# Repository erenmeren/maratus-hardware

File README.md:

# maratus-hardware

Open hardware for **Maratus** (maratus.co): the **Core** (an always-powered 4-inch touchscreen that
shows a cloud-triggered QR code), the **Dock** and the **LAN Module**. KiCad sources, mechanical
CAD and design documents.

**Status: draft.** Nothing here is manufacturing-ready, and no hardware has been built or tested.
The boards are generated and autorouted; the critical nets still need a layout engineer
(`docs/design-spec.md`, sections 10 and 11).

## Where to start

| Path | Content |
| --- | --- |
| `docs/design-spec.md` | The design decisions, block by block, and the open items |
| `hardware/core/` | KiCad project of the Core |
| `hardware/dock-contact/`, `hardware/dock-base/` | KiCad projects of the Dock's two boards |
| `mechanical/core/` | Enclosure (STEP, STL), cover lens (DXF and drawing) |
| `tools/` | Generators and checks; the commands are listed in `CLAUDE.md` |

Related repositories: `erenmeren/maratus-firmware` (ESP-IDF firmware) and `erenmeren/maratus-admin`
(cloud, device protocol).

## Licence

Apache License 2.0, see `LICENSE`. Copyright 2026 the Maratus authors.

Not covered by it: the datasheets and reference schematics in `docs/reference/`, which belong to
their manufacturers and are kept here for reference, and Espressif's KiCad library in
`hardware/lib/espressif`, a git submodule with its own licence.

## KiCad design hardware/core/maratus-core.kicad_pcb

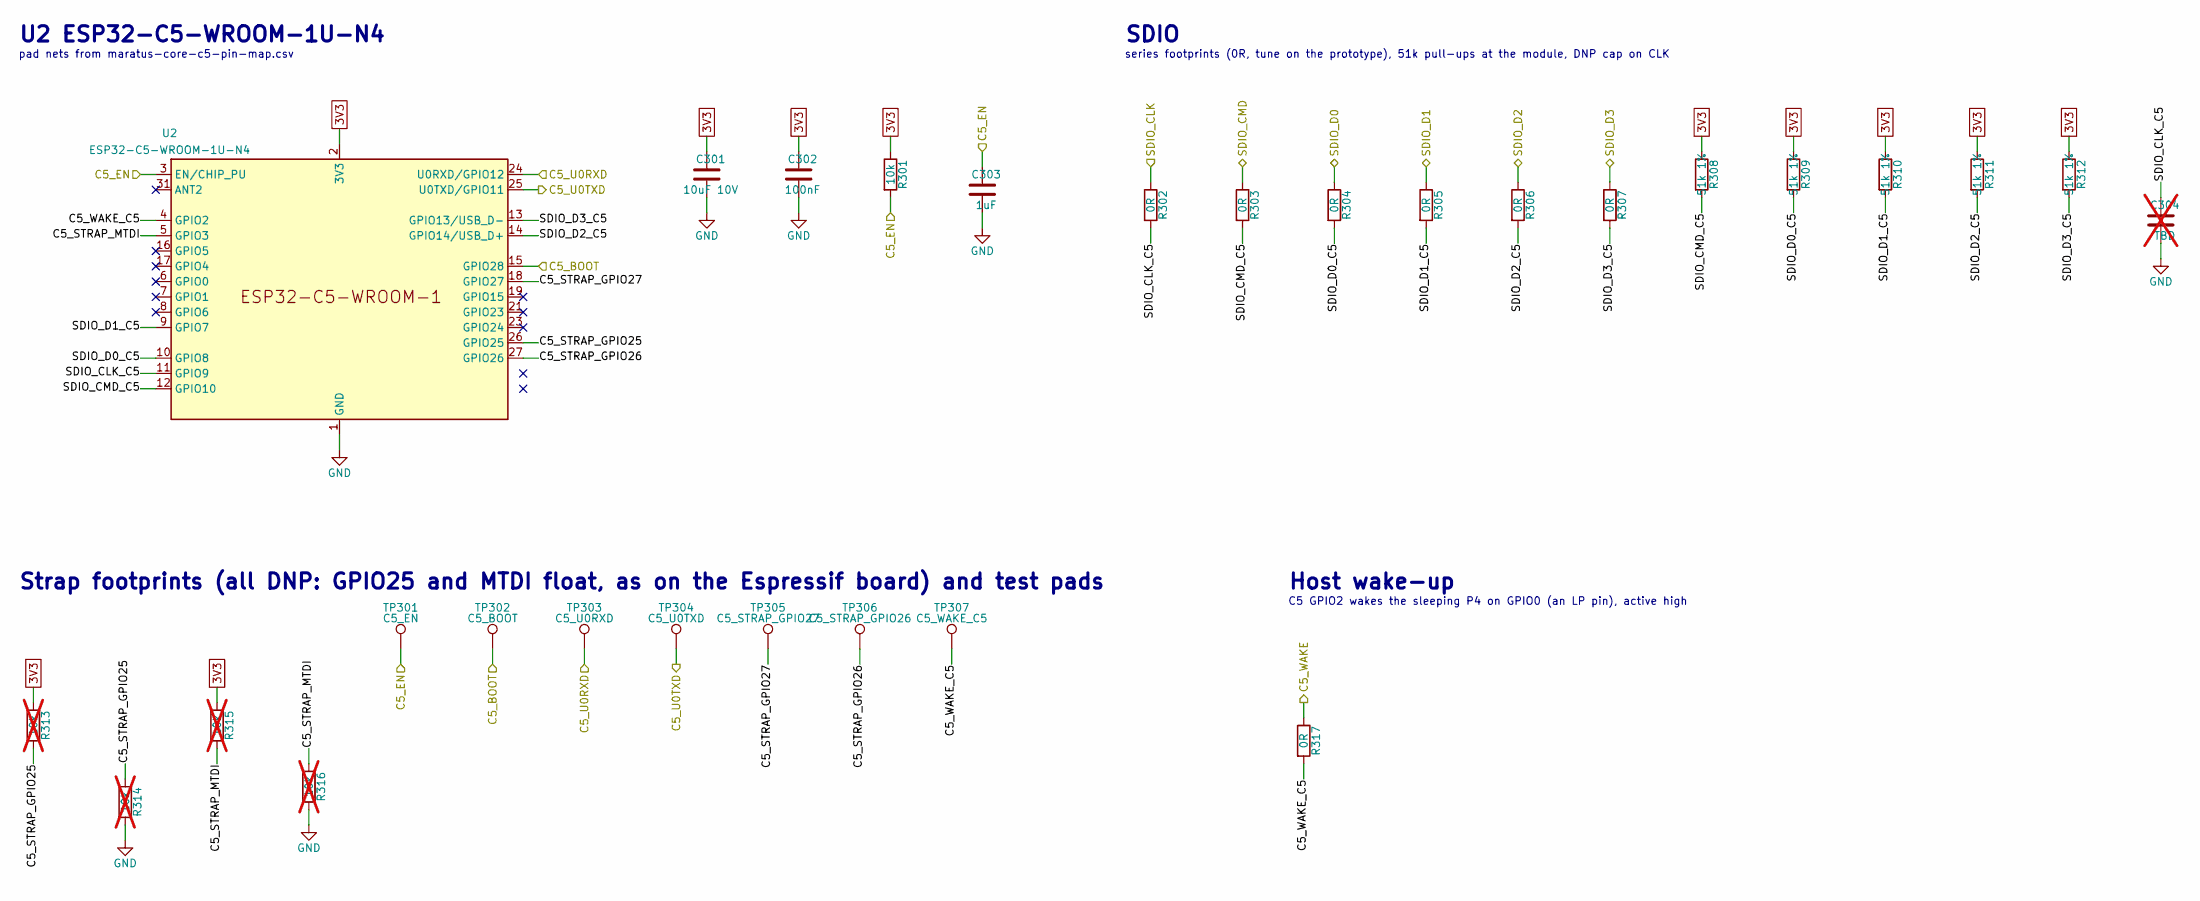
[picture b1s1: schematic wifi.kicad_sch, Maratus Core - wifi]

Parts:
C301: 10uF 10V; C_0805_2012Metric
C302: 100nF; C_0402_1005Metric
C303: 1uF; C_0402_1005Metric
C304: TBD; C_0402_1005Metric; not fitted
R301: 10k; R_0402_1005Metric
R302, R303, R304, R305, R306, R307, R317: 0R; R_0402_1005Metric
R308, R309, R310, R311, R312: 51k 1%; R_0402_1005Metric
R313, R314, R315, R316: 10k; R_0402_1005Metric; not fitted
TP301: C5_EN; TestPoint_Pad_D1.0mm
TP302: C5_BOOT; TestPoint_Pad_D1.0mm
TP303: C5_U0RXD; TestPoint_Pad_D1.0mm
TP304: C5_U0TXD; TestPoint_Pad_D1.0mm
TP305: C5_STRAP_GPIO27; TestPoint_Pad_D1.0mm
TP306: C5_STRAP_GPIO26; TestPoint_Pad_D1.0mm
TP307: C5_WAKE_C5; TestPoint_Pad_D1.0mm
U2: ESP32-C5-WROOM-1U-N4; ESP32-C5-WROOM-1U

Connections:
3V3: C301.1, C302.1, R301.1, R308.1, R309.1, R310.1, R311.1, R312.1, R313.1, R315.1, U2.2 (3V3); also elsewhere on the board
/C5_BOOT: TP302.1, U2.15 (GPIO28); also elsewhere on the board
/C5_EN: C303.1, R301.2, TP301.1, U2.3 (EN/CHIP_PU); also elsewhere on the board
/C5_U0RXD: TP303.1, U2.24 (U0RXD/GPIO12); also elsewhere on the board
/C5_U0TXD: TP304.1, U2.25 (U0TXD/GPIO11); also elsewhere on the board
/C5_WAKE: R317.1; also elsewhere on the board
/SDIO_CLK: R302.1; also elsewhere on the board
/SDIO_CMD: R303.1; also elsewhere on the board
/SDIO_D0: R304.1; also elsewhere on the board
/SDIO_D1: R305.1; also elsewhere on the board
/SDIO_D2: R306.1; also elsewhere on the board
/SDIO_D3: R307.1; also elsewhere on the board
/wifi/C5_STRAP_GPIO25: R313.2, R314.1, U2.26 (GPIO25)
/wifi/C5_STRAP_GPIO26: TP306.1, U2.27 (GPIO26)
/wifi/C5_STRAP_GPIO27: TP305.1, U2.18 (GPIO27)
/wifi/C5_STRAP_MTDI: R315.2, R316.1, U2.5 (GPIO3)
/wifi/C5_WAKE_C5: R317.2, TP307.1, U2.4 (GPIO2)
/wifi/SDIO_CLK_C5: C304.1, R302.2, U2.11 (GPIO9)
/wifi/SDIO_CMD_C5: R303.2, R308.2, U2.12 (GPIO10)
/wifi/SDIO_D0_C5: R304.2, R309.2, U2.10 (GPIO8)
/wifi/SDIO_D1_C5: R305.2, R310.2, U2.9 (GPIO7)
/wifi/SDIO_D2_C5: R306.2, R311.2, U2.14 (GPIO14/USB_D+)
/wifi/SDIO_D3_C5: R307.2, R312.2, U2.13 (GPIO13/USB_D-)
GND: C301.2, C302.2, C303.2, C304.2, R314.2, R316.2, U2.1 (GND), U2.28 (GND), U2.29 (GND), U2.30 (GND), U2.32 (GND); also elsewhere on the board

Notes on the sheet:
SDIO
U2 ESP32-C5-WROOM-1U-N4
C5 GPIO2 wakes the sleeping P4 on GPIO0 (an LP pin), active high
Host wake-up
Strap footprints (all DNP: GPIO25 and MTDI float, as on the Espressif board) and test pads
pad nets from maratus-core-c5-pin-map.csv
series footprints (0R, tune on the prototype), 51k pull-ups at the module, DNP cap on CLK

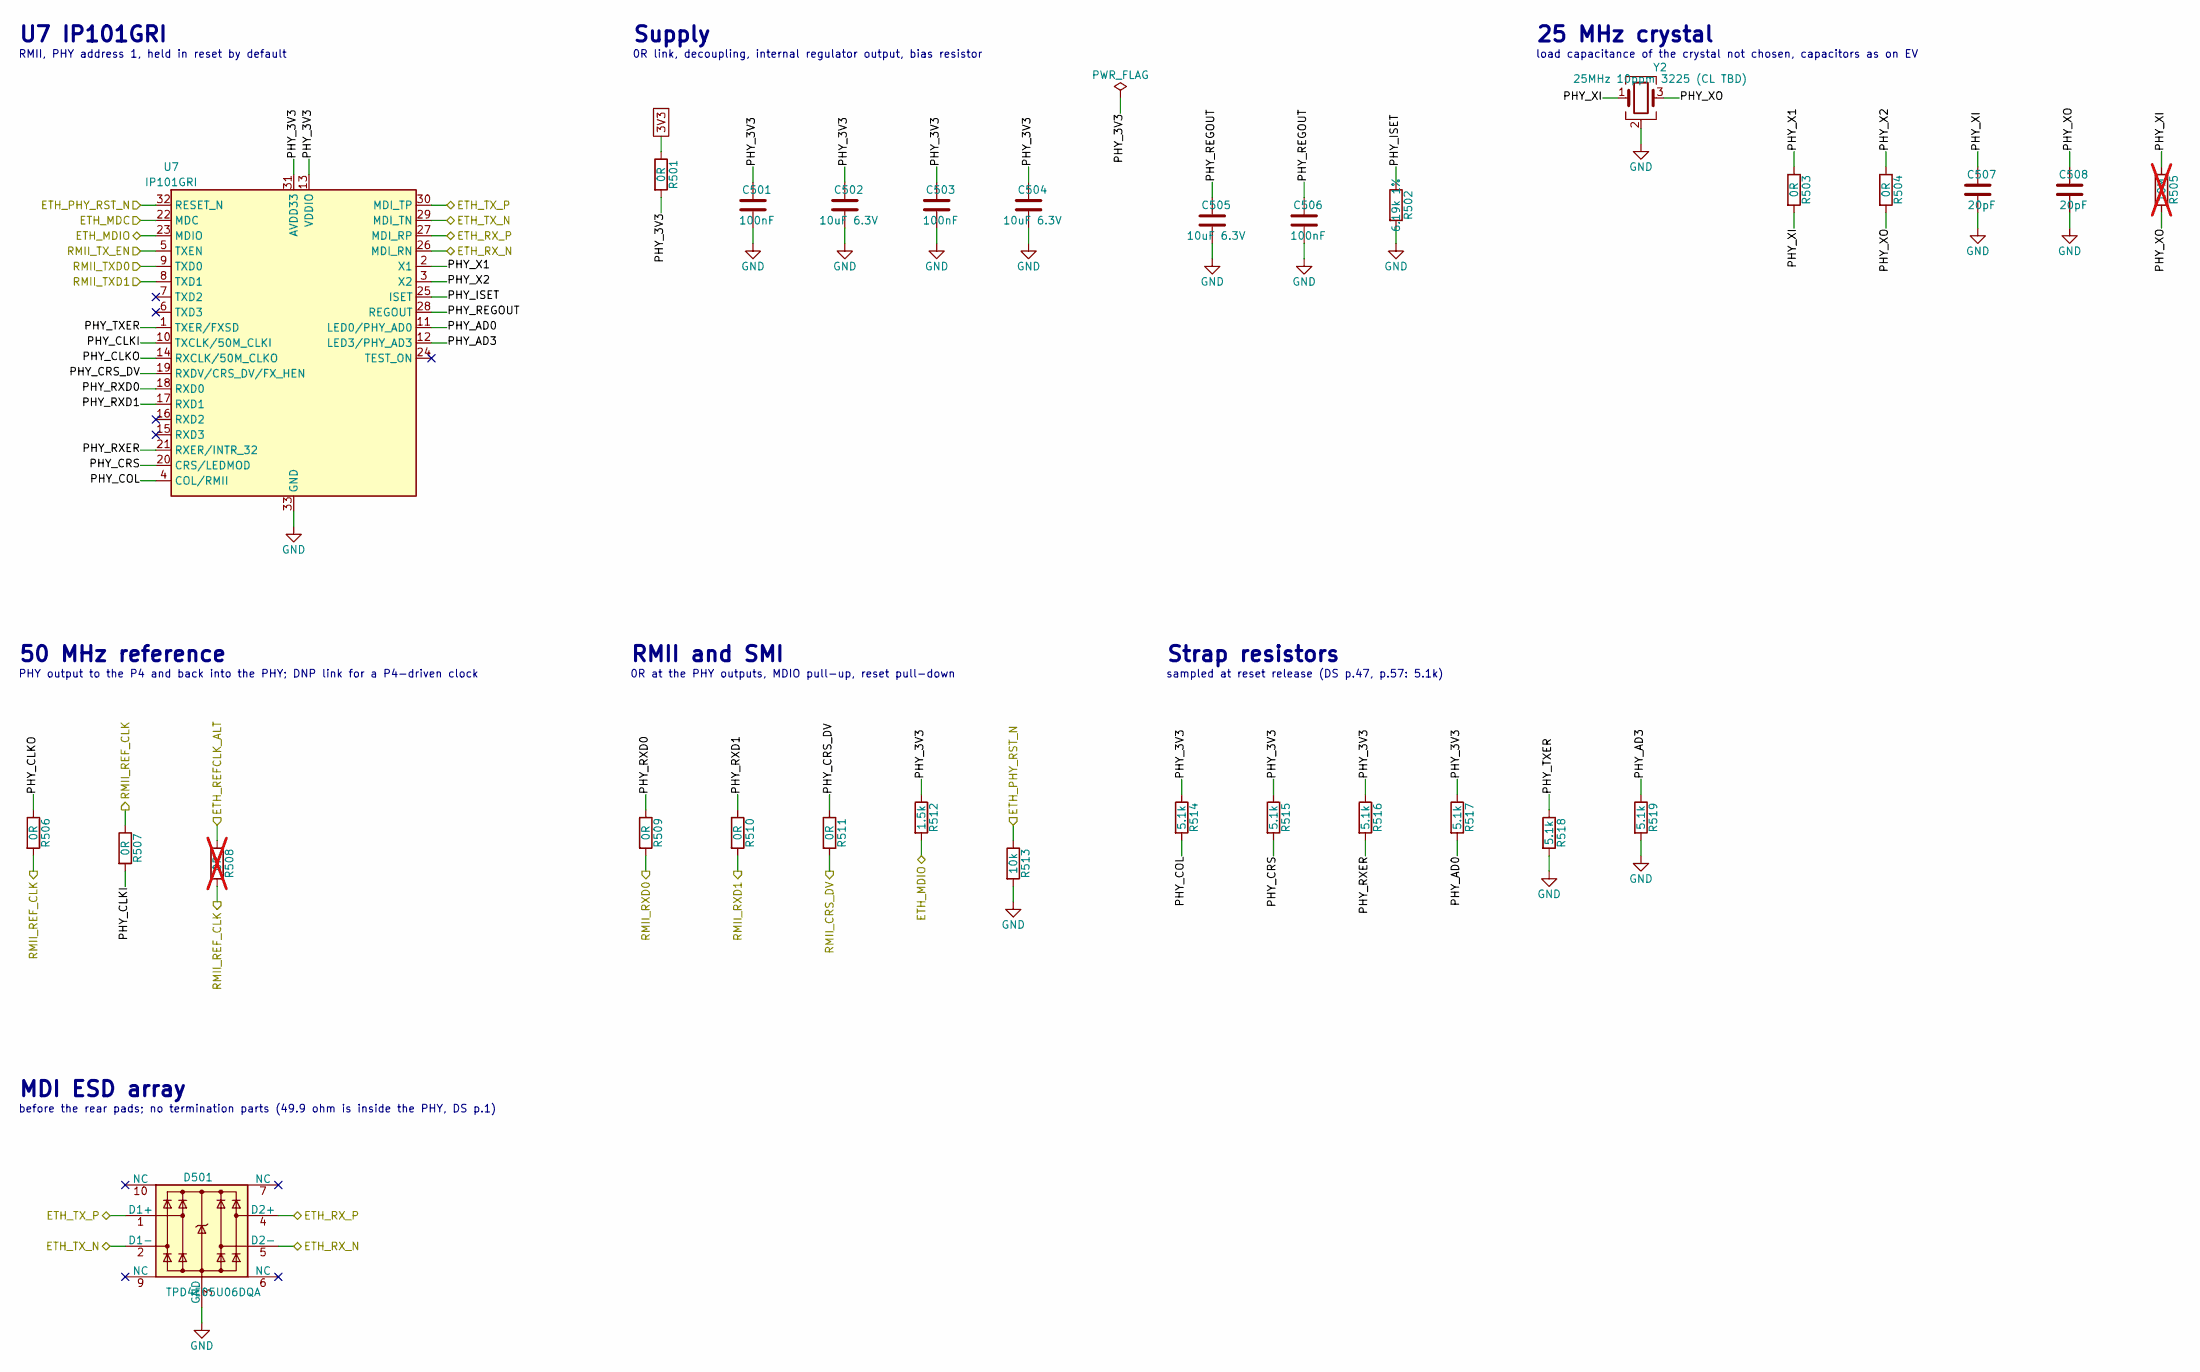
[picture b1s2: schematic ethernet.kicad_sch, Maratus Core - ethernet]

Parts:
C501, C503, C506: 100nF; C_0402_1005Metric
C502, C504, C505: 10uF 6.3V; C_0603_1608Metric
C507, C508: 20pF; C_0402_1005Metric
D501: TPD4E05U06DQA; USON-10_2.5x1.0mm_P0.5mm
R501, R503, R504, R506, R507, R509, R510, R511: 0R; R_0402_1005Metric
R502: 6.19k 1%; R_0402_1005Metric
R505: 10M; R_0402_1005Metric; not fitted
R508: 0R; R_0402_1005Metric; not fitted
R512: 1.5k; R_0402_1005Metric
R513: 10k; R_0402_1005Metric
R514, R515, R516, R517, R518, R519: 5.1k; R_0402_1005Metric
U7: IP101GRI; QFN-32-1EP_4x4mm_P0.4mm_EP2.65x2.65mm
Y2: 25MHz 10ppm 3225 (CL TBD); Crystal_SMD_3225-4Pin_3.2x2.5mm

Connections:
3V3: R501.1; also elsewhere on the board
/ETH_MDC: U7.22 (MDC); also elsewhere on the board
/ETH_MDIO: R512.2, U7.23 (MDIO); also elsewhere on the board
/ETH_PHY_RST_N: R513.1, U7.32 (RESET_N); also elsewhere on the board
/ETH_REFCLK_ALT: R508.1; also elsewhere on the board
/ETH_RX_N: D501.5 (D2-), U7.26 (MDI_RN); also elsewhere on the board
/ETH_RX_P: D501.4 (D2+), U7.27 (MDI_RP); also elsewhere on the board
/ETH_TX_N: D501.2 (D1-), U7.29 (MDI_TN); also elsewhere on the board
/ETH_TX_P: D501.1 (D1+), U7.30 (MDI_TP); also elsewhere on the board
/RMII_CRS_DV: R511.2; also elsewhere on the board
/RMII_REF_CLK: R506.2, R507.1, R508.2; also elsewhere on the board
/RMII_RXD0: R509.2; also elsewhere on the board
/RMII_RXD1: R510.2; also elsewhere on the board
/RMII_TXD0: U7.9 (TXD0); also elsewhere on the board
/RMII_TXD1: U7.8 (TXD1); also elsewhere on the board
/RMII_TX_EN: U7.5 (TXEN); also elsewhere on the board
/ethernet/PHY_3V3: C501.1, C502.1, C503.1, C504.1, R501.2, R512.1, R514.1, R515.1, R516.1, R517.1, U7.13 (VDDIO), U7.31 (AVDD33)
/ethernet/PHY_AD0: R517.2, U7.11 (LED0/PHY_AD0)
/ethernet/PHY_AD3: R519.1, U7.12 (LED3/PHY_AD3)
/ethernet/PHY_CLKI: R507.2, U7.10 (TXCLK/50M_CLKI)
/ethernet/PHY_CLKO: R506.1, U7.14 (RXCLK/50M_CLKO)
/ethernet/PHY_COL: R514.2, U7.4 (COL/RMII)
/ethernet/PHY_CRS: R515.2, U7.20 (CRS/LEDMOD)
/ethernet/PHY_CRS_DV: R511.1, U7.19 (RXDV/CRS_DV/FX_HEN)
/ethernet/PHY_ISET: R502.1, U7.25 (ISET)
/ethernet/PHY_REGOUT: C505.1, C506.1, U7.28 (REGOUT)
/ethernet/PHY_RXD0: R509.1, U7.18 (RXD0)
/ethernet/PHY_RXD1: R510.1, U7.17 (RXD1)
/ethernet/PHY_RXER: R516.2, U7.21 (RXER/INTR_32)
/ethernet/PHY_TXER: R518.1, U7.1 (TXER/FXSD)
/ethernet/PHY_X1: R503.1, U7.2 (X1)
/ethernet/PHY_X2: R504.1, U7.3 (X2)
/ethernet/PHY_XI: C507.1, R503.2, R505.1, Y2.1
/ethernet/PHY_XO: C508.1, R504.2, R505.2, Y2.3
GND: C501.2, C502.2, C503.2, C504.2, C505.2, C506.2, C507.2, C508.2, D501.3 (GND), D501.8 (GND), R502.2, R513.2, R518.2, R519.2, U7.33 (GND), Y2.2 (G), Y2.4 (G); also elsewhere on the board

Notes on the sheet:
before the rear pads; no termination parts (49.9 ohm is inside the PHY, DS p.1)
50 MHz reference
Supply
U7 IP101GRI
MDI ESD array
Strap resistors
load capacitance of the crystal not chosen, capacitors as on EV
0R link, decoupling, internal regulator output, bias resistor
RMII, PHY address 1, held in reset by default
0R at the PHY outputs, MDIO pull-up, reset pull-down
PHY output to the P4 and back into the PHY; DNP link for a P4-driven clock
RMII and SMI
25 MHz crystal
sampled at reset release (DS p.47, p.57: 5.1k)

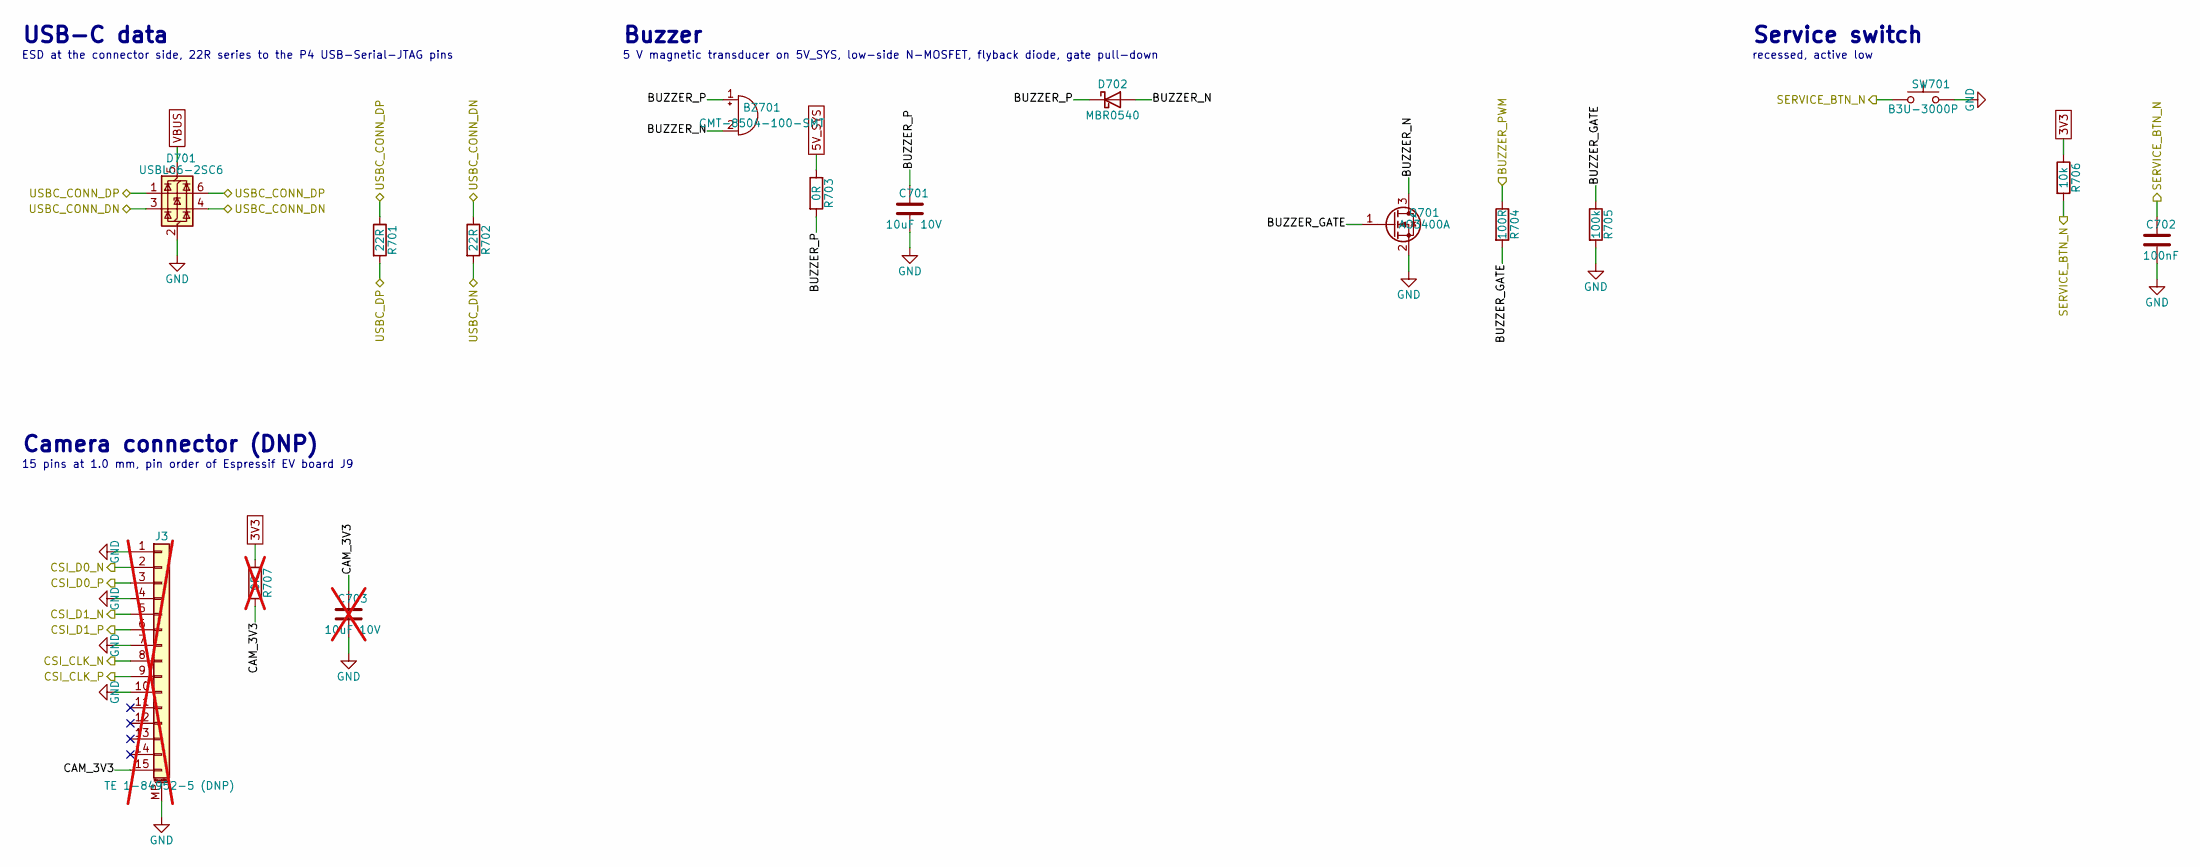
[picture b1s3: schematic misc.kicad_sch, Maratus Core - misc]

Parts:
BZ701: CMT-8504-100-SMT; MagneticBuzzer_CUI_CMT-8504-100-SMT
C701: 10uF 10V; C_0805_2012Metric
C702: 100nF; C_0402_1005Metric
C703: 10uF 10V; C_0805_2012Metric; not fitted
D701: USBLC6-2SC6; SOT-23-6
D702: MBR0540; D_SOD-123
J3: TE 1-84952-5 (DNP); TE_1-84952-5_1x15-1MP_P1.0mm_Horizontal; not fitted
Q701: AO3400A; SOT-23
R701, R702: 22R; R_0402_1005Metric
R703: 0R; R_0402_1005Metric
R704: 100R; R_0402_1005Metric
R705: 100k; R_0402_1005Metric
R706: 10k; R_0402_1005Metric
R707: 0R; R_0402_1005Metric; not fitted
SW701: B3U-3000P; SW_SPST_B3U-3000P

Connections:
3V3: R706.1, R707.1; also elsewhere on the board
5V_SYS: R703.1; also elsewhere on the board
/BUZZER_PWM: R704.1; also elsewhere on the board
/CSI_CLK_N: J3.8; also elsewhere on the board
/CSI_CLK_P: J3.9; also elsewhere on the board
/CSI_D0_N: J3.2; also elsewhere on the board
/CSI_D0_P: J3.3; also elsewhere on the board
/CSI_D1_N: J3.5; also elsewhere on the board
/CSI_D1_P: J3.6; also elsewhere on the board
/SERVICE_BTN_N: C702.1, R706.2, SW701.1; also elsewhere on the board
/USBC_CONN_DN: D701.3 (I/O2), D701.4 (I/O2), R702.1; also elsewhere on the board
/USBC_CONN_DP: D701.1 (I/O1), D701.6 (I/O1), R701.1; also elsewhere on the board
/USBC_DN: R702.2; also elsewhere on the board
/USBC_DP: R701.2; also elsewhere on the board
/misc/BUZZER_GATE: Q701.1 (G), R704.2, R705.1
/misc/BUZZER_N: BZ701.2 (-), D702.2 (A), Q701.3 (D)
/misc/BUZZER_P: BZ701.1 (+), C701.1, D702.1 (K), R703.2
/misc/CAM_3V3: C703.1, J3.15, R707.2
GND: C701.2, C702.2, C703.2, D701.2 (GND), J3.1, J3.4, J3.7, J3.10, J3.MP (MountPin), Q701.2 (S), R705.2, SW701.2; also elsewhere on the board
VBUS: D701.5 (VBUS); also elsewhere on the board

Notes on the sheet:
Service switch
Camera connector (DNP)
recessed, active low
Buzzer
15 pins at 1.0 mm, pin order of Espressif EV board J9
USB-C data
5 V magnetic transducer on 5V_SYS, low-side N-MOSFET, flyback diode, gate pull-down
ESD at the connector side, 22R series to the P4 USB-Serial-JTAG pins

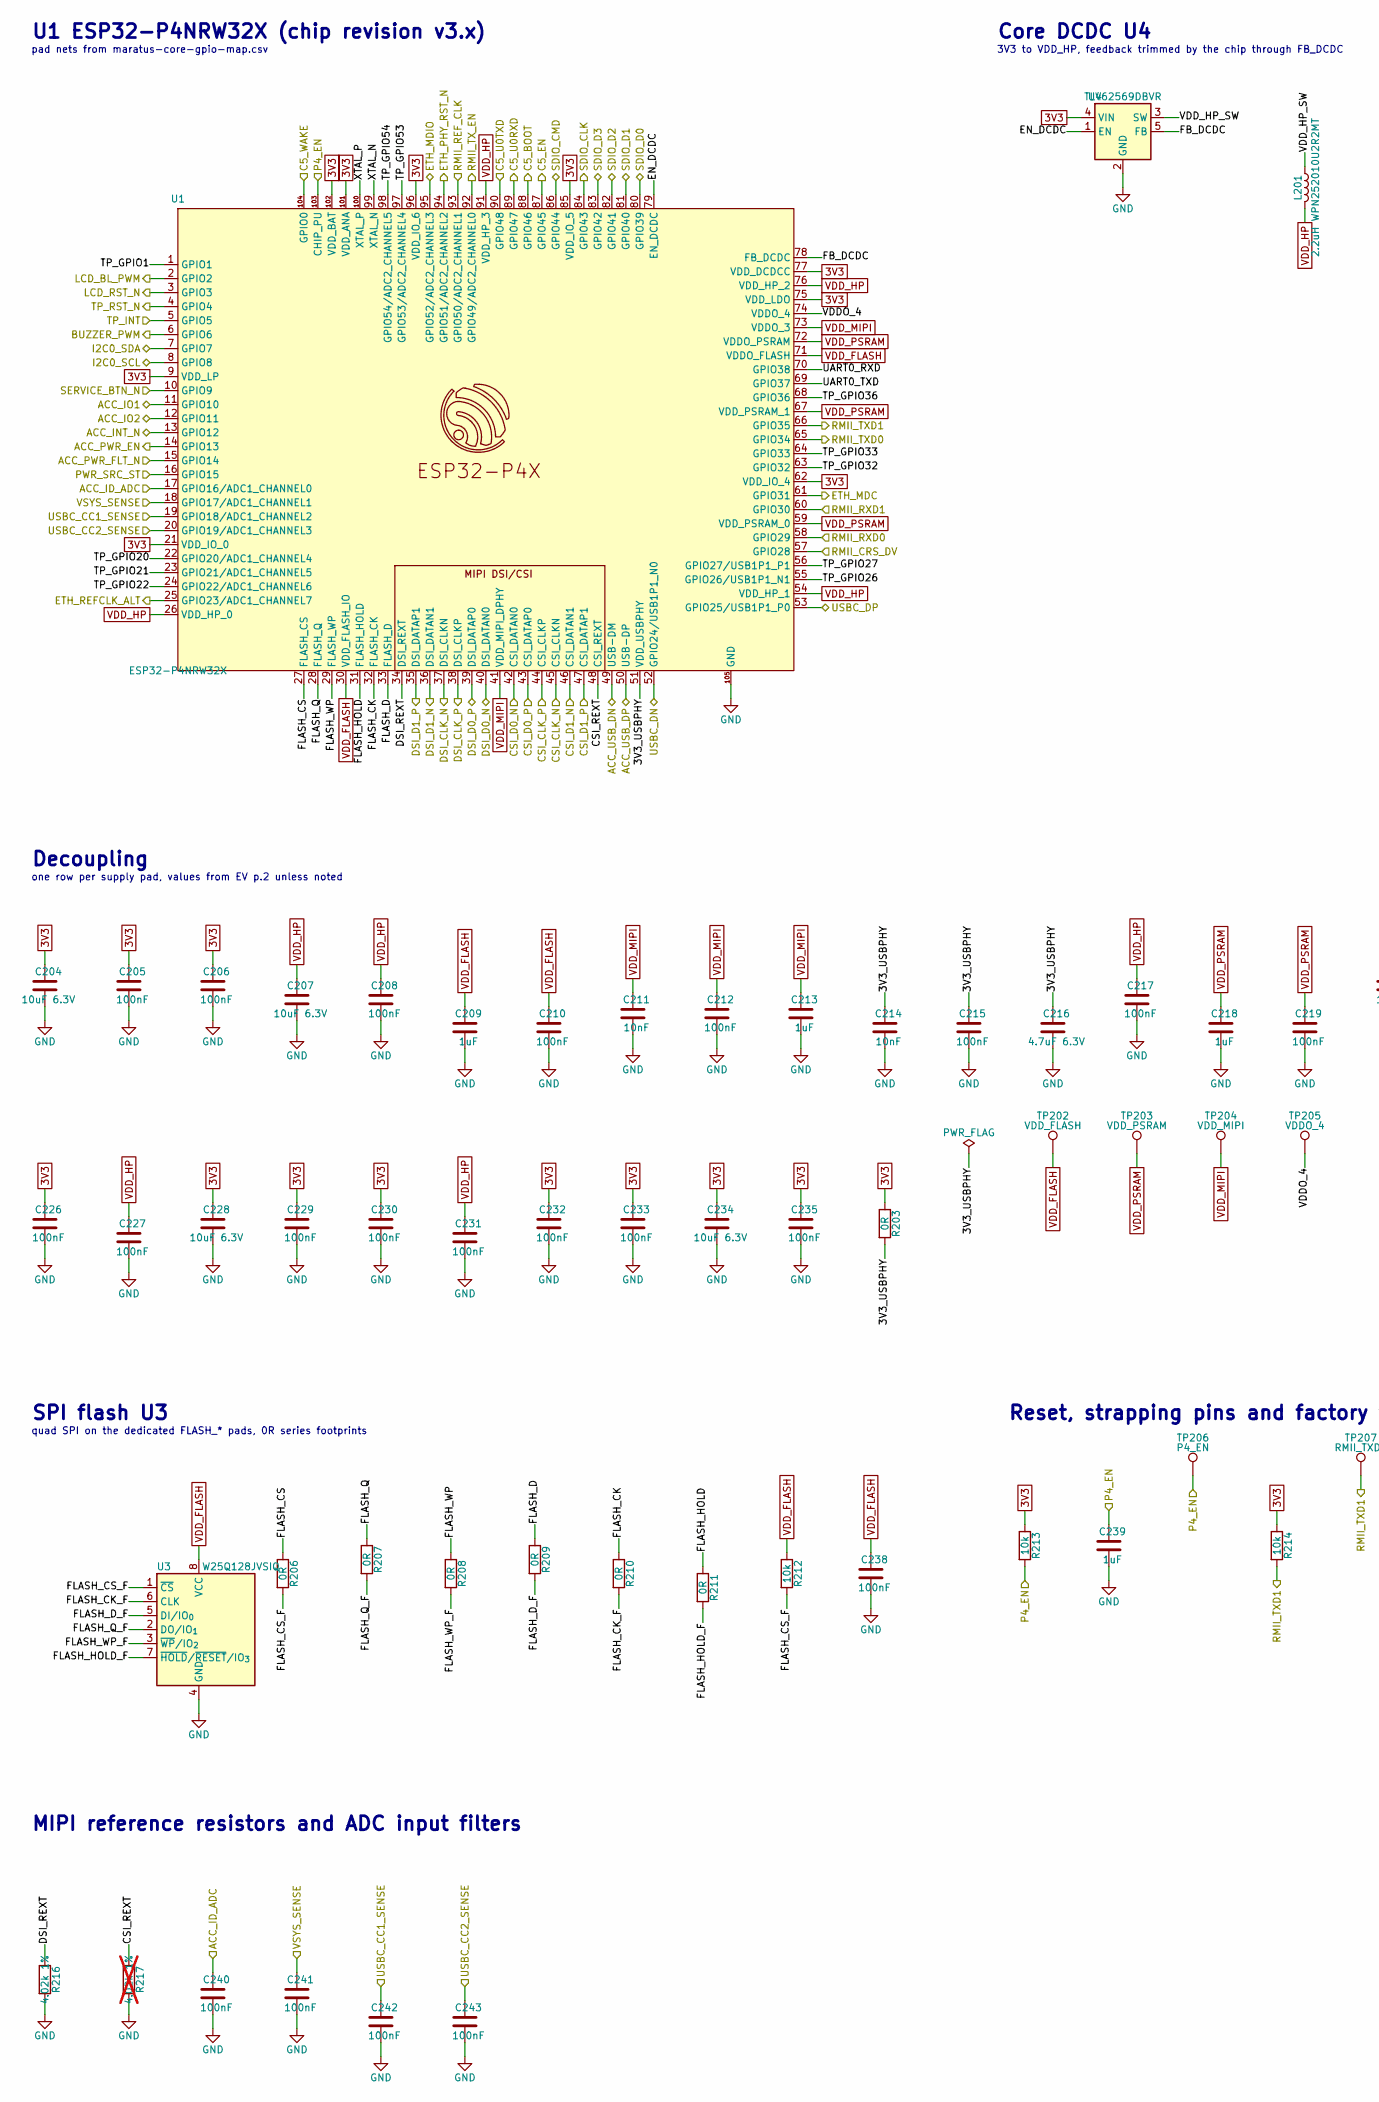
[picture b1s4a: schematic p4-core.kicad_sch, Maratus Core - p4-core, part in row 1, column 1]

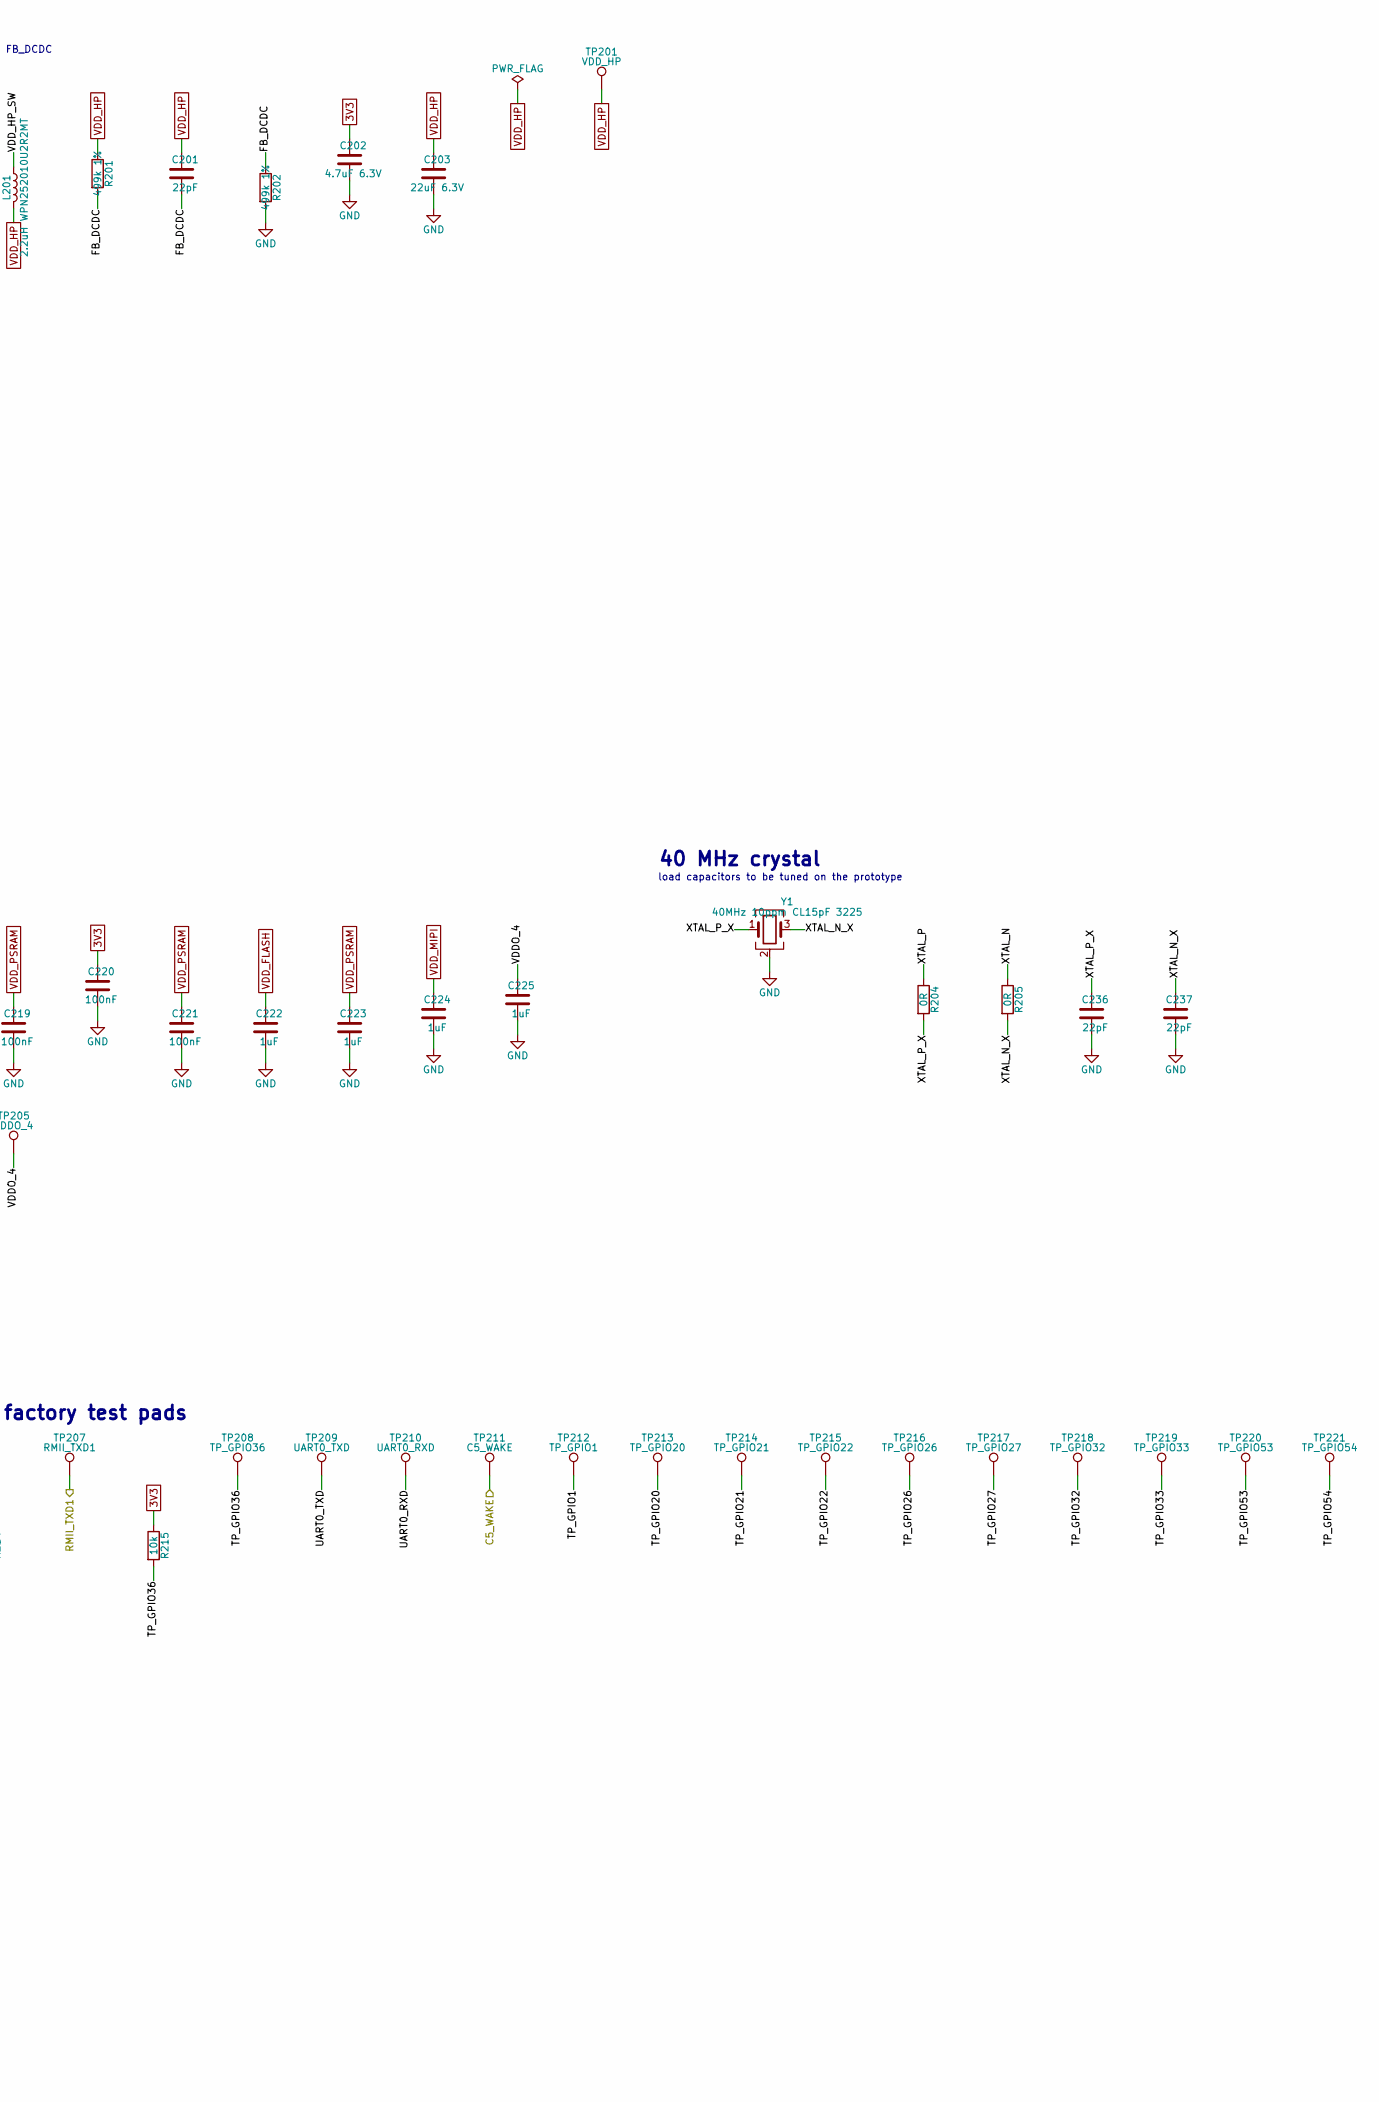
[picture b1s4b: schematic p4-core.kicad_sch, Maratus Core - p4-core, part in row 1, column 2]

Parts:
C201, C236, C237: 22pF; C_0402_1005Metric
C202, C216: 4.7uF 6.3V; C_0603_1608Metric
C203: 22uF 6.3V; C_0805_2012Metric
C204, C207, C228, C234: 10uF 6.3V; C_0603_1608Metric
C205, C206, C208, C210, C212, C215, C217, C219, C220, C221, C226, C227, C229, C230, C231, C232, C233, C235, C238, C240, C241, C242, C243: 100nF; C_0402_1005Metric
C209, C213, C218, C222, C223, C224, C225, C239: 1uF; C_0402_1005Metric
C211, C214: 10nF; C_0402_1005Metric
L201: 2.2uH WPN252010U2R2MT; L_1008_2520Metric
R201, R202: 499k 1%; R_0402_1005Metric
R203, R204, R205, R206, R207, R208, R209, R210, R211: 0R; R_0402_1005Metric
R212, R213, R214, R215: 10k; R_0402_1005Metric
R216: 4.02k 1%; R_0402_1005Metric
R217: 4.02k 1%; R_0402_1005Metric; not fitted
TP201: VDD_HP; TestPoint_Pad_D1.0mm
TP202: VDD_FLASH; TestPoint_Pad_D1.0mm
TP203: VDD_PSRAM; TestPoint_Pad_D1.0mm
TP204: VDD_MIPI; TestPoint_Pad_D1.0mm
TP205: VDDO_4; TestPoint_Pad_D1.0mm
TP206: P4_EN; TestPoint_Pad_D1.0mm
TP207: RMII_TXD1; TestPoint_Pad_D1.0mm
TP208: TP_GPIO36; TestPoint_Pad_D1.0mm
TP209: UART0_TXD; TestPoint_Pad_D1.0mm
TP210: UART0_RXD; TestPoint_Pad_D1.0mm
TP211: C5_WAKE; TestPoint_Pad_D1.0mm
TP212: TP_GPIO1; TestPoint_Pad_D1.0mm
TP213: TP_GPIO20; TestPoint_Pad_D1.0mm
TP214: TP_GPIO21; TestPoint_Pad_D1.0mm
TP215: TP_GPIO22; TestPoint_Pad_D1.0mm
TP216: TP_GPIO26; TestPoint_Pad_D1.0mm
TP217: TP_GPIO27; TestPoint_Pad_D1.0mm
TP218: TP_GPIO32; TestPoint_Pad_D1.0mm
TP219: TP_GPIO33; TestPoint_Pad_D1.0mm
TP220: TP_GPIO53; TestPoint_Pad_D1.0mm
TP221: TP_GPIO54; TestPoint_Pad_D1.0mm
U1: ESP32-P4NRW32X; ESP32-P4
U3: W25Q128JVSIQ; SOIC-8_5.3x5.3mm_P1.27mm
U4: TLV62569DBVR; SOT-23-5
Y1: 40MHz 10ppm CL15pF 3225; Crystal_SMD_3225-4Pin_3.2x2.5mm

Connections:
3V3: C202.1, C204.1, C205.1, C206.1, C220.1, C226.1, C228.1, C229.1, C230.1, C232.1, C233.1, C234.1, C235.1, R203.1, R213.1, R214.1, R215.1, U1.9 (VDD_LP), U1.21 (VDD_IO_0), U1.62 (VDD_IO_4), U1.75 (VDD_LDO), U1.77 (VDD_DCDCC), U1.85 (VDD_IO_5), U1.96 (VDD_IO_6), U1.101 (VDD_ANA), U1.102 (VDD_BAT), U4.4 (VIN); also elsewhere on the board
/ACC_ID_ADC: C240.1, U1.17 (GPIO16/ADC1_CHANNEL0); also elsewhere on the board
/ACC_INT_N: U1.13 (GPIO12); also elsewhere on the board
/ACC_IO1: U1.11 (GPIO10); also elsewhere on the board
/ACC_IO2: U1.12 (GPIO11); also elsewhere on the board
/ACC_PWR_EN: U1.14 (GPIO13); also elsewhere on the board
/ACC_PWR_FLT_N: U1.15 (GPIO14); also elsewhere on the board
/ACC_USB_DN: U1.49 (USB-DM); also elsewhere on the board
/ACC_USB_DP: U1.50 (USB-DP); also elsewhere on the board
/BUZZER_PWM: U1.6 (GPIO6); also elsewhere on the board
/C5_BOOT: U1.88 (GPIO46); also elsewhere on the board
/C5_EN: U1.87 (GPIO45); also elsewhere on the board
/C5_U0RXD: U1.89 (GPIO47); also elsewhere on the board
/C5_U0TXD: U1.90 (GPIO48); also elsewhere on the board
/C5_WAKE: TP211.1, U1.104 (GPIO0); also elsewhere on the board
/CSI_CLK_N: U1.45 (CSI_CLKN); also elsewhere on the board
/CSI_CLK_P: U1.44 (CSI_CLKP); also elsewhere on the board
/CSI_D0_N: U1.42 (CSI_DATAN0); also elsewhere on the board
/CSI_D0_P: U1.43 (CSI_DATAP0); also elsewhere on the board
/CSI_D1_N: U1.46 (CSI_DATAN1); also elsewhere on the board
/CSI_D1_P: U1.47 (CSI_DATAP1); also elsewhere on the board
/DSI_CLK_N: U1.37 (DSI_CLKN); also elsewhere on the board
/DSI_CLK_P: U1.38 (DSI_CLKP); also elsewhere on the board
/DSI_D0_N: U1.40 (DSI_DATAN0); also elsewhere on the board
/DSI_D0_P: U1.39 (DSI_DATAP0); also elsewhere on the board
/DSI_D1_N: U1.36 (DSI_DATAN1); also elsewhere on the board
/DSI_D1_P: U1.35 (DSI_DATAP1); also elsewhere on the board
/ETH_MDC: U1.61 (GPIO31); also elsewhere on the board
/ETH_MDIO: U1.95 (GPIO52/ADC2_CHANNEL3); also elsewhere on the board
/ETH_PHY_RST_N: U1.94 (GPIO51/ADC2_CHANNEL2); also elsewhere on the board
/ETH_REFCLK_ALT: U1.25 (GPIO23/ADC1_CHANNEL7); also elsewhere on the board
/I2C0_SCL: U1.8 (GPIO8); also elsewhere on the board
/I2C0_SDA: U1.7 (GPIO7); also elsewhere on the board
/LCD_BL_PWM: U1.2 (GPIO2); also elsewhere on the board
/LCD_RST_N: U1.3 (GPIO3); also elsewhere on the board
/P4_EN: C239.1, R213.2, TP206.1, U1.103 (CHIP_PU); also elsewhere on the board
/PWR_SRC_ST: U1.16 (GPIO15); also elsewhere on the board
/RMII_CRS_DV: U1.57 (GPIO28); also elsewhere on the board
/RMII_REF_CLK: U1.93 (GPIO50/ADC2_CHANNEL1); also elsewhere on the board
/RMII_RXD0: U1.58 (GPIO29); also elsewhere on the board
/RMII_RXD1: U1.60 (GPIO30); also elsewhere on the board
/RMII_TXD0: U1.65 (GPIO34); also elsewhere on the board
/RMII_TXD1: R214.2, TP207.1, U1.66 (GPIO35); also elsewhere on the board
/RMII_TX_EN: U1.92 (GPIO49/ADC2_CHANNEL0); also elsewhere on the board
/SDIO_CLK: U1.84 (GPIO43); also elsewhere on the board
/SDIO_CMD: U1.86 (GPIO44); also elsewhere on the board
/SDIO_D0: U1.80 (GPIO39); also elsewhere on the board
/SDIO_D1: U1.81 (GPIO40); also elsewhere on the board
/SDIO_D2: U1.82 (GPIO41); also elsewhere on the board
/SDIO_D3: U1.83 (GPIO42); also elsewhere on the board
/SERVICE_BTN_N: U1.10 (GPIO9); also elsewhere on the board
/TP_INT: U1.5 (GPIO5); also elsewhere on the board
/TP_RST_N: U1.4 (GPIO4); also elsewhere on the board
/USBC_CC1_SENSE: C242.1, U1.19 (GPIO18/ADC1_CHANNEL2); also elsewhere on the board
/USBC_CC2_SENSE: C243.1, U1.20 (GPIO19/ADC1_CHANNEL3); also elsewhere on the board
/USBC_DN: U1.52 (GPIO24/USB1P1_N0); also elsewhere on the board
/USBC_DP: U1.53 (GPIO25/USB1P1_P0); also elsewhere on the board
/VSYS_SENSE: C241.1, U1.18 (GPIO17/ADC1_CHANNEL1); also elsewhere on the board
/p4-core/3V3_USBPHY: C214.1, C215.1, C216.1, R203.2, U1.51 (VDD_USBPHY)
/p4-core/CSI_REXT: R217.1, U1.48 (CSI_REXT)
/p4-core/DSI_REXT: R216.1, U1.34 (DSI_REXT)
/p4-core/EN_DCDC: U1.79 (EN_DCDC), U4.1 (EN)
/p4-core/FB_DCDC: C201.2, R201.2, R202.1, U1.78 (FB_DCDC), U4.5 (FB)
/p4-core/FLASH_CK: R210.1, U1.32 (FLASH_CK)
/p4-core/FLASH_CK_F: R210.2, U3.6 (CLK)
/p4-core/FLASH_CS: R206.1, U1.27 (FLASH_CS)
/p4-core/FLASH_CS_F: R206.2, R212.2, U3.1 (~CS)
/p4-core/FLASH_D: R209.1, U1.33 (FLASH_D)
/p4-core/FLASH_D_F: R209.2, U3.5 (DI/IO_{0})
/p4-core/FLASH_HOLD: R211.1, U1.31 (FLASH_HOLD)
/p4-core/FLASH_HOLD_F: R211.2, U3.7 (~HOLD/~RESET/IO_{3})
/p4-core/FLASH_Q: R207.1, U1.28 (FLASH_Q)
/p4-core/FLASH_Q_F: R207.2, U3.2 (DO/IO_{1})
/p4-core/FLASH_WP: R208.1, U1.29 (FLASH_WP)
/p4-core/FLASH_WP_F: R208.2, U3.3 (~WP/IO_{2})
/p4-core/TP_GPIO1: TP212.1, U1.1 (GPIO1)
/p4-core/TP_GPIO20: TP213.1, U1.22 (GPIO20/ADC1_CHANNEL4)
/p4-core/TP_GPIO21: TP214.1, U1.23 (GPIO21/ADC1_CHANNEL5)
/p4-core/TP_GPIO22: TP215.1, U1.24 (GPIO22/ADC1_CHANNEL6)
/p4-core/TP_GPIO26: TP216.1, U1.55 (GPIO26/USB1P1_N1)
/p4-core/TP_GPIO27: TP217.1, U1.56 (GPIO27/USB1P1_P1)
/p4-core/TP_GPIO32: TP218.1, U1.63 (GPIO32)
/p4-core/TP_GPIO33: TP219.1, U1.64 (GPIO33)
/p4-core/TP_GPIO36: R215.2, TP208.1, U1.68 (GPIO36)
/p4-core/TP_GPIO53: TP220.1, U1.97 (GPIO53/ADC2_CHANNEL4)
/p4-core/TP_GPIO54: TP221.1, U1.98 (GPIO54/ADC2_CHANNEL5)
/p4-core/UART0_RXD: TP210.1, U1.70 (GPIO38)
/p4-core/UART0_TXD: TP209.1, U1.69 (GPIO37)
/p4-core/VDDO_4: C225.1, TP205.1, U1.74 (VDDO_4)
/p4-core/VDD_HP_SW: L201.1, U4.3 (SW)
/p4-core/XTAL_N: R205.1, U1.99 (XTAL_N)
/p4-core/XTAL_N_X: C237.1, R205.2, Y1.3
/p4-core/XTAL_P: R204.1, U1.100 (XTAL_P)
/p4-core/XTAL_P_X: C236.1, R204.2, Y1.1
GND: C202.2, C203.2, C204.2, C205.2, C206.2, C207.2, C208.2, C209.2, C210.2, C211.2, C212.2, C213.2, C214.2, C215.2, C216.2, C217.2, C218.2, C219.2, C220.2, C221.2, C222.2, C223.2, C224.2, C225.2, C226.2, C227.2, C228.2, C229.2, C230.2, C231.2, C232.2, C233.2, C234.2, C235.2, C236.2, C237.2, C238.2, C239.2, C240.2, C241.2, C242.2, C243.2, R202.2, R216.2, R217.2, U1.105 (GND), U3.4 (GND), U4.2 (GND), Y1.2 (G), Y1.4 (G); also elsewhere on the board
VDD_FLASH: C209.1, C210.1, C222.1, C238.1, R212.1, TP202.1, U1.30 (VDD_FLASH_IO), U1.71 (VDDO_FLASH), U3.8 (VCC)
VDD_HP: C201.1, C203.1, C207.1, C208.1, C217.1, C227.1, C231.1, L201.2, R201.1, TP201.1, U1.26 (VDD_HP_0), U1.54 (VDD_HP_1), U1.76 (VDD_HP_2), U1.91 (VDD_HP_3)
VDD_MIPI: C211.1, C212.1, C213.1, C224.1, TP204.1, U1.41 (VDD_MIPI_DPHY), U1.73 (VDDO_3)
VDD_PSRAM: C218.1, C219.1, C221.1, C223.1, TP203.1, U1.59 (VDD_PSRAM_0), U1.67 (VDD_PSRAM_1), U1.72 (VDDO_PSRAM)

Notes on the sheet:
3V3 to VDD_HP, feedback trimmed by the chip through FB_DCDC
Reset, strapping pins and factory test pads
load capacitors to be tuned on the prototype
pad nets from maratus-core-gpio-map.csv
Decoupling
quad SPI on the dedicated FLASH_* pads, 0R series footprints
MIPI reference resistors and ADC input filters
Core DCDC U4
SPI flash U3
40 MHz crystal
U1 ESP32-P4NRW32X (chip revision v3.x)
one row per supply pad, values from EV p.2 unless noted
